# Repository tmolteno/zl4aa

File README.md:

# ZL4AA Radio Projects

Author: Tim Molteno (ZL4TCM)

Some very basic radios, developed as a way to learn about radio.

## SDR

Very basic radio project. It uses the CH32V305RBT6 RISC-V microprocessor (http://www.wch-ic.com/downloads/CH32V20x_30xDS0_PDF.html). It has the following features
made by Nanjing Qinheng Microelectronics Co. 

* 144 MHz 32-bit RISC-V core (IMAFC instructions)
* Single cycle multiply and hardware division (FPU)
* 64K SRAM
* 4 Op Amps
* 2 x 12-bit DAC !MHz (Dual Channel Mode available for Baseband)
* 2 x 12-bit ADC 1MHz

Reference manual (http://www.wch-ic.com/downloads/CH32FV2x_V3xRM_PDF.html)

### IMAFC

Set of RISC-V instruction extensions.

Integer (M) multiply and divide.
Atomic (A) instructions
Floating Point (F) single-precision
Compressed (C) instructions.

## Architecture

A local oscillator with I/Q outputs.

A switching I/Q mixer to zero IF.

40 dB LNA on Antenna Input for RX.

DAC I,Q -> MIXER -> HPF -> PA

## Gui.

SPI OLED screen, LED, Button1, Button2, Morse Key. Beep through speaker.

## Basic 6m Morse TX

Set LO to 50 MHz. 

Button 1. Increase f
Button 3. Decrease f,
Button 3 ON. Tx on (beep)

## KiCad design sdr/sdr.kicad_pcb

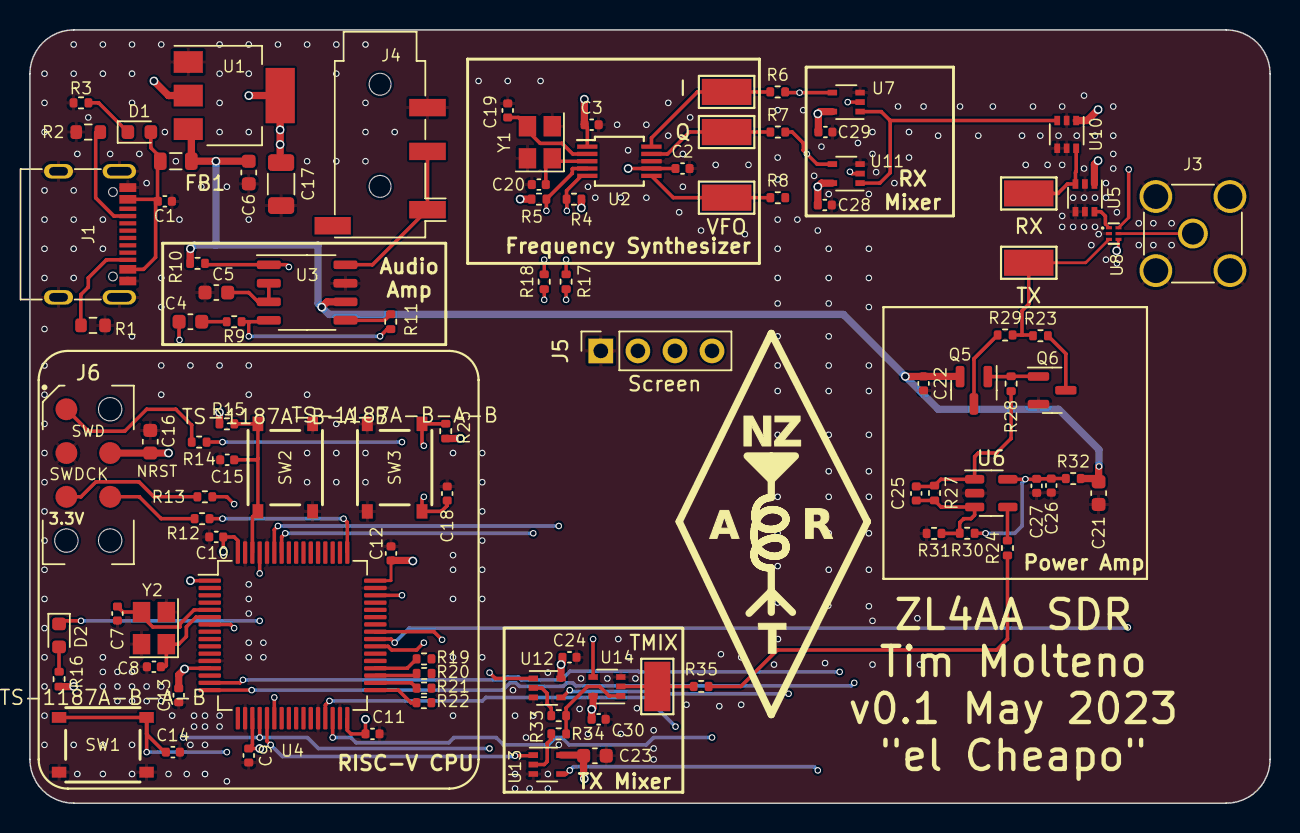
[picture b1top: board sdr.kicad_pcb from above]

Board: 4 copper layers, 85.0 x 53.0 mm, 98 parts (0 on the bottom side), 65 nets.

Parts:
C1, C9, C10, C11, C12, C13, C28, C29, C30: 10n; C_0402_1005Metric
C2, C3, C14, C15, C18, C22, C24, C26: 100n; C_0402_1005Metric
C4: 330n; C_0603_1608Metric
C5, C6, C21, C23: 1u; C_0603_1608Metric
C7, C8: 12p; C_0402_1005Metric
C16: 470n; C_0603_1608Metric
C17: 22u; C_1206_3216Metric
C19, C20: 2.2p; C_0402_1005Metric
C25: 0.5pF; C_0402_1005Metric
C27: 1n; C_0402_1005Metric
D1: PWR; D_0603_1608Metric
D2: PB8; D_0603_1608Metric
FB1: GZ2012D101TF; L_0805_2012Metric
J1: USB_C_Receptacle_USB2.0; USB_C_Receptacle_ SHOU_HAN_TYPE-C 16PIN 2MD(073)
J3: Conn_Coaxial; SMA_Amphenol_901-144_Vertical
J4: PJ-320D; Jack_3.5mm_PJ320D_Horizontal
J5: Screen; PinSocket_1x04_P2.54mm_Vertical
J6: swd-connect-5; swd-connect-5-mcu
Q5: AO3400A; SOT-23
Q6: AO3401A; SOT-23
R1, R2: 5.1k; R_0603_1608Metric
R3, R30, R31: 470; R_0402_1005Metric
R4, R5, R10, R15, R25: 10k; R_0402_1005Metric
R6, R7, R8, R35: 0; R_0402_1005Metric
R9, R11: 20k; R_0402_1005Metric
R12, R13, R14, R17, R18, R19, R20, R21, R22, R28: 100; R_0402_1005Metric
R16: 1k; R_0402_1005Metric
R23, R29: 10; R_0402_1005Metric
R24: 120; R_0402_1005Metric
R27: 220; R_0402_1005Metric
R32: 1; R_0402_1005Metric
R33, R34: 47; R_0402_1005Metric
SW1, SW2, SW3: TS-1187A-B-A-B
TP1: VFO; TestPoint_Keystone_5015_Micro-Minature
TP2: Q; TestPoint_Keystone_5015_Micro-Minature
TP3: I; TestPoint_Keystone_5015_Micro-Minature
TP4: RX; TestPoint_Keystone_5015_Micro-Minature
TP5: TX; TestPoint_Keystone_5015_Micro-Minature
TP6: TMIX; TestPoint_Keystone_5015_Micro-Minature
U1: AMS1117-3.3; SOT-223-3_TabPin2
U2: MS5351M; MSOP-10_3x3mm_P0.5mm
U3: LM4871M/TR_C383075; SOP-8_3.9x4.9mm_P1.27mm
U4: CH32V305RBT6; LQFP-64_10x10mm_P0.5mm
U5, U10: BGA2817; SOT-363_SC-70-6
U6: GS8091-TR; SOT-23-5
U7, U11, U12, U13, U14: 74LVC1G66; SOT-353_SC-70-5
U8: FM1630C; DFN-6_L1.1-W0.7-P0.40-BL
Y1, Y2: 25MHz; Crystal_SMD_3225-4Pin_3.2x2.5mm

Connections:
+3.3V: C2.1, C3.1, C9.1, C10.1, C11.1, C12.1, C13.1, C16.1, C17.1, C23.1, C24.1, C28.1, C29.1, C30.1, J5.2, J6.3 (3V3), R4.2, R5.1, R15.1, R16.1, R25.1, U1.2 (VO), U2.1 (VDD), U2.7 (VDDO), U4.1 (VBAT), U4.13 (VDDA), U4.19 (VDD_4), U4.32 (VIO_1), U4.48 (VDD_2), U4.64 (VIO_3), U5.1 (Vcc), U7.5 (VCC), U8.4 (VDD), U10.1 (Vcc), U11.5 (VCC), U12.5 (VCC), U13.5 (VCC), U14.5 (VCC)
+5P: C26.1, C27.1, R30.1, R32.1, U6.5 (V+)
+5V: C6.1, C21.1, C22.1, FB1.2, Q5.2 (S), R10.1, R32.2, U1.3 (VI), U3.6 (VDD)
/Audio Output/AUDIO: C4.2, U4.20 (PA4/ADC4/DAC0), U12.1
/Audio Output/SHUTDOWN: R10.2, U3.1 (Shutdown), U4.22 (PA6/ADC6)
/CPU/ADC_I: U4.15 (PA1/ADC1), U7.2
/CPU/ADC_Q: U4.16 (PA2/ADC2), U11.2
/CPU/DAC_Q: U4.21 (PA5/ADC5/DAC1), U13.1
/CPU/I2C_SCL: R5.2, R18.2, U2.4 (SCL)
/CPU/I2C_SDA: R4.1, R17.2, U2.5 (SDA)
/Freq Synthesizer/LO_I: R6.2, U7.4, U12.4
/Freq Synthesizer/LO_Q: R7.2, U11.4, U13.4
/Mixer I/RF: U7.1, U10.3, U11.1
/TX Amplifier/RF_IN: R24.2, R35.2
/TX Amplifier/RF_OUT: R23.1, R29.2, TP5.1, U8.3 (RF1)
/Tx Mixers/RF_OUT: R35.1, TP6.1, U14.2
GND: C1.2, C2.2, C3.2, C5.2, C6.2, C7.1, C8.1, C9.2, C10.2, C11.2, C12.2, C13.2, C14.2, C15.2, C16.2, C17.2, C18.2, C19.1, C20.2, C21.2, C22.2, C23.2, C24.2, C26.2, C27.2, C28.2, C29.2, C30.2, J1.A1 (GND), J1.A12 (GND), J1.B1 (GND), J1.B12 (GND), J1.S1 (SHIELD), J3.2 (Ext), J4.R2, J5.1, J6.2 (GND), Q6.2 (S), R1.2, R2.2, R3.2, R31.2, SW1.1, SW2.1, SW3.1, U1.1 (GND), U2.8 (GND), U3.7 (GND), U4.12 (VSSA), U4.18 (VSS_4), U4.28 (PB2/BOOT1), U4.31 (VSS_1), U4.47 (VSS_2), U4.60 (BOOT0), U4.63 (VSS_3), U5.2 (G), U5.4 (G), U5.5 (G), U6.2 (V-), U7.3 (GND), U8.2 (GND), U10.2 (G), U10.4 (G), U10.5 (G), U11.3 (GND), U12.3 (GND), U13.3 (GND), U14.3 (GND), Y1.2, Y1.4, Y2.2, Y2.4
KEY: C15.1, R15.2, SW2.2, U4.62 (PB9)
LED: D2.1 (K), U4.61 (PB8)
LEFT: J4.R1, J4.T, U3.8 (VO2)
NRST: C14.1, R13.1, SW1.2, U4.7 (NRST)
unnamed: C4.1, R9.1
unnamed: C25.1, R27.1, R28.1, U6.1
unnamed: C1.1, D1.2 (A), FB1.1, J1.A4 (VBUS), J1.A9 (VBUS), J1.B4 (VBUS), J1.B9 (VBUS)
unnamed: D1.1 (K), R3.1
unnamed: D2.2 (A), R16.2
unnamed: J1.A5 (CC1), R2.1
unnamed: J1.B5 (CC2), R1.1
unnamed: J3.1 (In), U8.5 (ANT)
unnamed: J6.4 (RST), R13.2
unnamed: J6.5 (SWCLK), R12.2
unnamed: J6.1 (SWD), R14.2
unnamed: Q5.3 (D), R29.1
unnamed: Q5.1 (G), Q6.1 (G), R28.2
unnamed: Q6.3 (D), R23.2
unnamed: R33.1, U12.2
unnamed: R33.2, R34.1, U14.1
unnamed: R34.2, U13.2
unnamed: TP4.1, U5.3, U10.6
unnamed: R6.1, TP3.1, U2.10 (CLK0)
unnamed: R7.1, TP2.1, U2.9 (CLK1)
unnamed: R8.1, TP1.1, U2.6 (CLK2)
unnamed: C19.2, U2.2 (XA), Y1.3
unnamed: C20.1, U2.3 (XB), Y1.1
unnamed: C5.1, U3.2 (Bypass), U3.3 (+IN)
unnamed: R9.2, R11.1, U3.4 (-IN)
unnamed: R11.2, U3.5 (VO1)
unnamed: C7.2, U4.5 (OSC_IN/PD0), Y2.3
unnamed: C8.2, U4.6 (OSC_OUT/PD1), Y2.1
unnamed: R18.1, U4.58 (PB6/USB2DM)
unnamed: R17.1, U4.59 (PB7/USB2DP)
unnamed: R22.2, U4.33 (PB12)
unnamed: R21.2, U4.34 (PB13)
unnamed: R20.2, U4.35 (PB14)
unnamed: R19.2, U4.36 (PB15)
unnamed: R24.1, U6.4 (-)
unnamed: U5.6, U8.1 (RF2)
OLED_SCL: J5.3, U4.29 (PB10)
OLED_SDA: J5.4, U4.30 (PB11)
PTT: C18.1, R25.2, SW3.2, U4.39 (PC8)
RX_EN: U4.40 (PC9), U8.6 (VCTL)
SWCLK: R12.1, U4.49 (PA14/SWCLK)
SWDIO: R14.1, U4.46 (PA13/SWDIO)
TXMIX_EN: U4.41 (PA8), U14.4
V_BIAS: C25.2, R27.2, R30.2, R31.1, U6.3 (+)

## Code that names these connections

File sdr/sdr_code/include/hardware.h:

#ifndef __hardware_h__
#define __haredware_h__

#define BLINKY_GPIO_PIN GPIO_Pin_8
#define BLINKY_GPIO_PORT GPIOB


#define I2C_SCL_PIN GPIO_Pin_6
#define I2C_SDA_PIN GPIO_Pin_7

#define DAC_I_PIN GPIO_Pin_4
#define DAC_Q_PIN GPIO_Pin_5
#define AUDIO_SHUTDOWN_PIN GPIO_Pin_6

#define DAC_I_PORT GPIOA
#define DAC_Q_PORT GPIOA
#define AUDIO_SHUTDOWN_PORT GPIOA


#define PTT_KEY_PIN GPIO_Pin_8
#define PTT_KEY_PORT GPIOC

#define MODE_KEY_PIN GPIO_Pin_9
#define MODE_KEY_PORT GPIOB


void GPIO_Pins_Init(void);
void DAC_Initialize(void);
void DAC_Timer_Init(u16 arr,u16 psc);

void DAC_DMA_Init(u16* dacbuff16bit_ptr, u32 buffsize);
void Synthesizer_Init(u32 bound, u16 address);

int PTT_Pressed(void);
int Mode_Pressed(void);

void AudioEnable(void);
void AudioShutdown(void);

#endif // __hardware_h__

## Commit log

2023-03-14 Added microprocessor
2023-03-14 Update README to add some basic info
2023-03-14 Add author
2023-03-14 More info
2023-03-17 Added 3.3V LDO and CPU sheet
2023-03-17 Added CH32V CPU to symbols
2023-03-20 Update lots of things. Now have basic CPU as well as some crude mixers
2023-03-24 Added ST-link 6-pin 0.1 programming header
2023-03-25 Tighten up design layout.
2023-03-25 Added tx amp and mixer
2023-03-30 Updated the mixer to include some dedicated switches (Gainsail goes to 300 MHz)
2023-04-05 Many fixes. Updated mixers to use the analog switches rather than discretes.
2023-05-08 Added basic simulation
2023-05-08 Update schematic to kicad 7. Add IQ correction to models
2023-05-08 Graph titles
2023-05-10 Update to KiCAD 7
2023-05-10 Add a transmission simulation
2023-05-17 Add a start with transmission
2023-05-19 Complete layout
2023-05-19 First version 0.1 completed
2023-05-19 Update the via size. Reduce footprints outside board.
2023-05-20 Convert to a 4-layer board.
2023-05-20 Update logo to work with silkscreen layers
2023-05-20 Move logo to its own folder
2023-06-08 Added code first draft
2023-06-09 Shell of synthesizer going
2023-06-11 Modify the I2C address to shift it left by one bit??!. I2C now works
2023-06-13 Added a quadrature synthesis algorithm
2023-06-14 Add corrected quadrature synthesis code with band plans
2023-06-15 Refactor to multiple files
2023-06-15 Add symbols and footprints for SWD-Connect
2023-06-19 Removed connect-5
2023-06-19 Update footprints, and add an swd-connect-5
2023-06-19 DAC is going
2023-06-19 I have interrupts going
2023-06-20 Added extra pullup resistors on the OLED i2C. Changed the Synthesizer pullups to 2.2k from 10k
2023-06-20 Now with space invaders and a splash screen
2023-06-23 Space invaders is going!
2023-06-24 Adding u8g2 as a library dependency
2023-06-24 Added a going u8g2 library!
2023-06-26 Now using a better u8g2 space invaders
2023-06-26 Use new algorithms for hardware
